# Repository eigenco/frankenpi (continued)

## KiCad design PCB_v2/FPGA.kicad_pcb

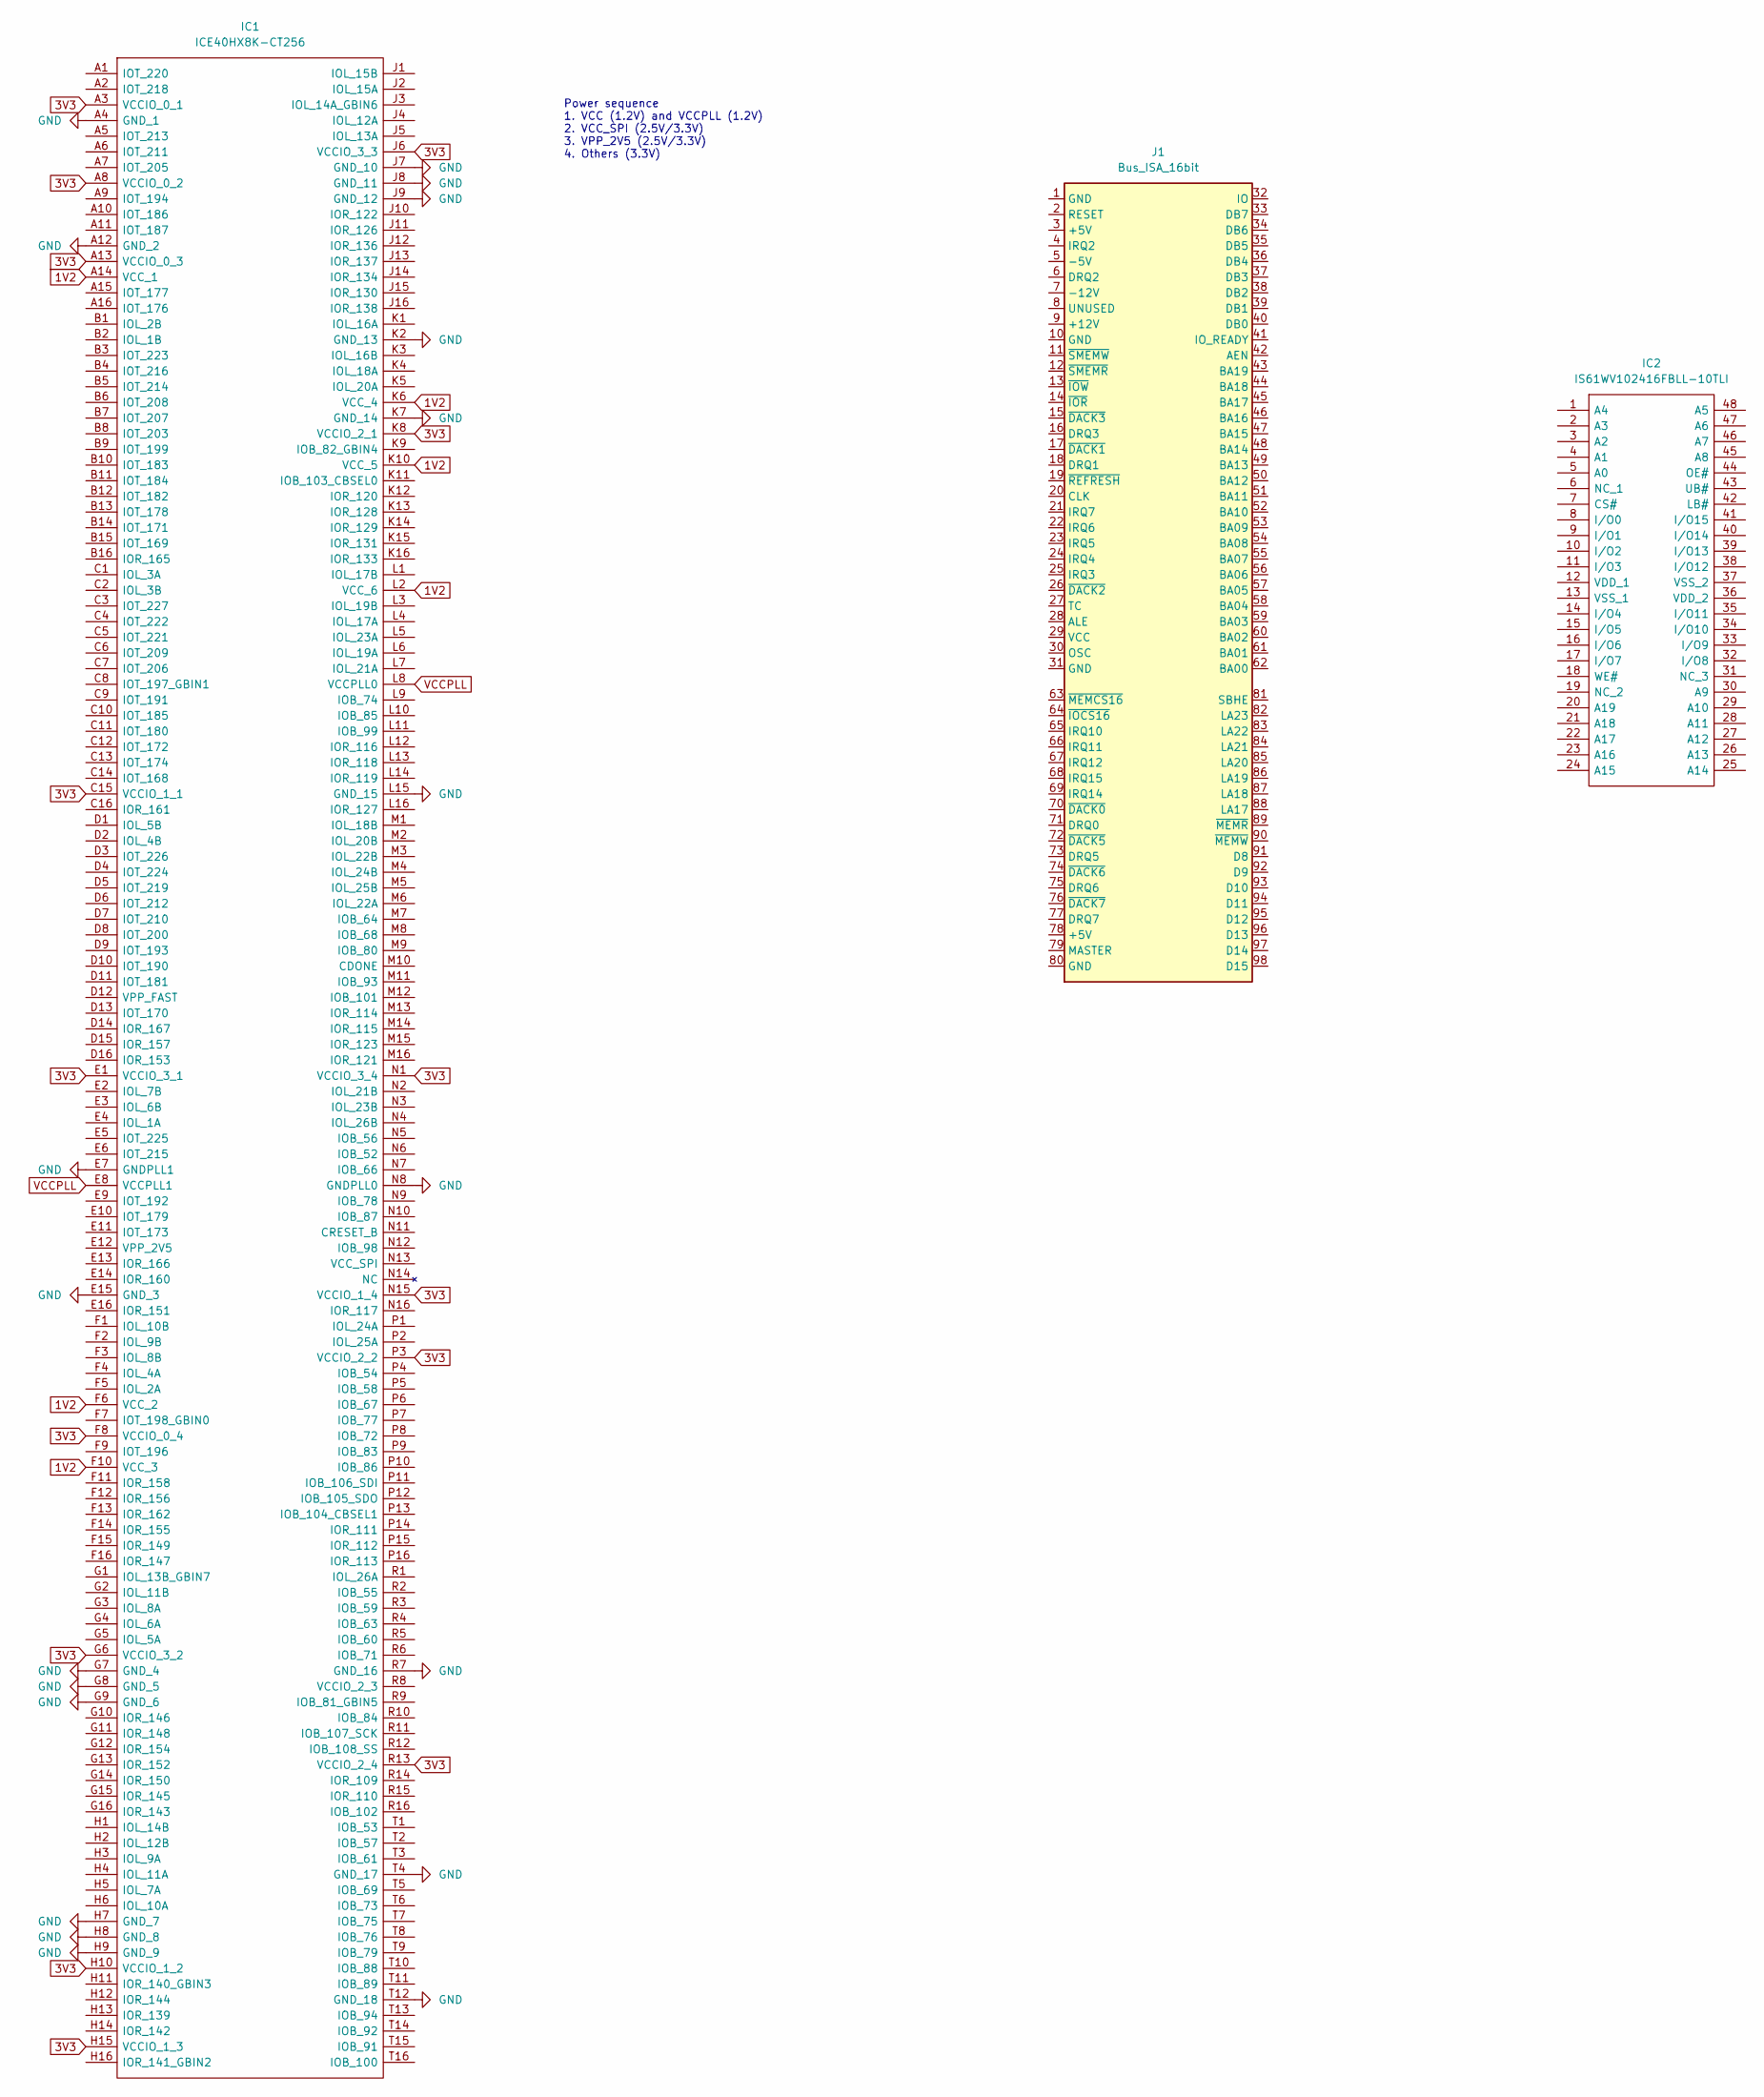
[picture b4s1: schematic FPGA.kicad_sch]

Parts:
IC1: ICE40HX8K-CT256; BGA256C80P16X16_1400X1400X170; Mouser Part Number 842-ICE40HX8K-CT256
IC2: IS61WV102416FBLL-10TLI; SOP50P2000X120-48N; Mouser Part Number 870-61WV12416FBL1TLI
J1: Bus_ISA_16bit; BUS_AT

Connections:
1V2: IC1.A14 (VCC_1), IC1.F6 (VCC_2), IC1.F10 (VCC_3), IC1.K6 (VCC_4), IC1.K10 (VCC_5), IC1.L2 (VCC_6)
3V3: IC1.A3 (VCCIO_0_1), IC1.A8 (VCCIO_0_2), IC1.A13 (VCCIO_0_3), IC1.C15 (VCCIO_1_1), IC1.E1 (VCCIO_3_1), IC1.F8 (VCCIO_0_4), IC1.G6 (VCCIO_3_2), IC1.H10 (VCCIO_1_2), IC1.H15 (VCCIO_1_3), IC1.J6 (VCCIO_3_3), IC1.K8 (VCCIO_2_1), IC1.N1 (VCCIO_3_4), IC1.N15 (VCCIO_1_4), IC1.P3 (VCCIO_2_2), IC1.R13 (VCCIO_2_4)
GND: IC1.A4 (GND_1), IC1.A12 (GND_2), IC1.E7 (GNDPLL1), IC1.E15 (GND_3), IC1.G7 (GND_4), IC1.G8 (GND_5), IC1.G9 (GND_6), IC1.H7 (GND_7), IC1.H8 (GND_8), IC1.H9 (GND_9), IC1.J7 (GND_10), IC1.J8 (GND_11), IC1.J9 (GND_12), IC1.K2 (GND_13), IC1.K7 (GND_14), IC1.L15 (GND_15), IC1.N8 (GNDPLL0), IC1.R7 (GND_16), IC1.T4 (GND_17), IC1.T12 (GND_18)
VCCPLL: IC1.E8 (VCCPLL1), IC1.L8 (VCCPLL0)

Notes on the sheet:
Power sequence 1. VCC (1.2V) and VCCPLL (1.2V) 2. VCC_SPI (2.5V/3.3V) 3. VPP_2V5 (2.5V/3.3V) 4. Others (3.3V)

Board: 2 copper layers, 3 parts (0 on the bottom side), 4 nets, no tracks yet.

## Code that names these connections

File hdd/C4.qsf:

# -------------------------------------------------------------------------- #
#
# Copyright (C) 1991-2013 Altera Corporation
# Your use of Altera Corporation's design tools, logic functions 
# and other software and tools, and its AMPP partner logic 
# functions, and any output files from any of the foregoing 
# (including device programming or simulation files), and any 
# associated documentation or information are expressly subject 
# to the terms and conditions of the Altera Program License 
# Subscription Agreement, Altera MegaCore Function License 
# Agreement, or other applicable license agreement, including, 
# without limitation, that your use is for the sole purpose of 
# programming logic devices manufactured by Altera and sold by 
# Altera or its authorized distributors.  Please refer to the 
# applicable agreement for further details.
#
# -------------------------------------------------------------------------- #
#
# Quartus II 64-Bit
# Version 13.0.1 Build 232 06/12/2013 Service Pack 1 SJ Web Edition
# Date created = 14:09:58  December 04, 2021
#
# -------------------------------------------------------------------------- #
#
# Notes:
#
# 1) The default values for assignments are stored in the file:
#		C4_assignment_defaults.qdf
#    If this file doesn't exist, see file:
#		assignment_defaults.qdf
#
# 2) Altera recommends that you do not modify this file. This
#    file is updated automatically by the Quartus II software
#    and any changes you make may be lost or overwritten.
#
# -------------------------------------------------------------------------- #


set_global_assignment -name FAMILY "Cyclone IV E"
set_global_assignment -name DEVICE EP4CE6E22C8
set_global_assignment -name TOP_LEVEL_ENTITY C4
set_global_assignment -name ORIGINAL_QUARTUS_VERSION "13.0 SP1"
set_global_assignment -name PROJECT_CREATION_TIME_DATE "14:09:58  DECEMBER 04, 2021"
set_global_assignment -name LAST_QUARTUS_VERSION "13.0 SP1"
set_global_assignment -name PROJECT_OUTPUT_DIRECTORY output_files
set_global_assignment -name MIN_CORE_JUNCTION_TEMP 0
set_global_assignment -name MAX_CORE_JUNCTION_TEMP 85
set_global_assignment -name ERROR_CHECK_FREQUENCY_DIVISOR 1
set_global_assignment -name NOMINAL_CORE_SUPPLY_VOLTAGE 1.2V

set_location_assignment PIN_25 -to clk
set_location_assignment PIN_138 -to leds[0]
set_location_assignment PIN_141 -to leds[1]
set_location_assignment PIN_142 -to leds[2]
set_location_assignment PIN_143 -to leds[3]
set_location_assignment PIN_144 -to leds[4]
set_location_assignment PIN_1 -to leds[5]
set_location_assignment PIN_2 -to leds[6]
set_location_assignment PIN_3 -to leds[7]

set_global_assignment -name PARTITION_NETLIST_TYPE SOURCE -section_id Top
set_global_assignment -name PARTITION_FITTER_PRESERVATION_LEVEL PLACEMENT_AND_ROUTING -section_id Top
set_global_assignment -name PARTITION_COLOR 16764057 -section_id Top
set_global_assignment -name STRATIX_DEVICE_IO_STANDARD "2.5 V"
set_location_assignment PIN_49 -to A[9]
set_location_assignment PIN_51 -to A[8]
set_location_assignment PIN_50 -to A[7]
set_location_assignment PIN_46 -to A[6]
set_location_assignment PIN_39 -to A[5]
set_location_assignment PIN_34 -to A[4]
set_location_assignment PIN_32 -to A[3]
set_location_assignment PIN_30 -to A[2]
set_location_assignment PIN_11 -to A[1]
set_location_assignment PIN_7 -to A[0]
set_location_assignment PIN_53 -to D[7]
set_location_assignment PIN_55 -to D[6]
set_location_assignment PIN_59 -to D[5]
set_location_assignment PIN_64 -to D[4]
set_location_assignment PIN_66 -to D[3]
set_location_assignment PIN_68 -to D[2]
set_location_assignment PIN_70 -to D[1]
set_location_assignment PIN_72 -to D[0]
set_location_assignment PIN_77 -to IOW
set_location_assignment PIN_80 -to IOR
set_location_assignment PIN_75 -to MEMW
set_location_assignment PIN_76 -to MEMR
set_location_assignment PIN_129 -to GPIO0
set_location_assignment PIN_126 -to GPIO1
set_location_assignment PIN_100 -to GPIO2
set_location_assignment PIN_85 -to GPIO3
set_location_assignment PIN_104 -to GPIO4
set_location_assignment PIN_128 -to GPIO5
set_location_assignment PIN_132 -to GPIO6
set_location_assignment PIN_127 -to GPIO7
set_location_assignment PIN_125 -to GPIO8
set_location_assignment PIN_120 -to GPIO9
set_location_assignment PIN_115 -to GPIO10
set_location_assignment PIN_67 -to IRQ2
set_location_assignment PIN_52 -to IRQ3
set_location_assignment PIN_54 -to IRQ4
set_location_assignment PIN_58 -to IRQ5
set_location_assignment PIN_60 -to IRQ6
set_location_assignment PIN_65 -to IRQ7
set_location_assignment PIN_33 -to DRQ1
set_location_assignment PIN_38 -to DACK1
set_location_assignment PIN_84 -to SPDIF
set_location_assignment PIN_124 -to GPIO11
set_location_assignment PIN_133 -to GPIO12
set_location_assignment PIN_136 -to GPIO13
set_location_assignment PIN_105 -to GPIO14
set_location_assignment PIN_110 -to GPIO15
set_location_assignment PIN_135 -to GPIO16
set_location_assignment PIN_106 -to GPIO17
set_location_assignment PIN_31 -to GPIO18
set_location_assignment PIN_28 -to GPIO19
set_location_assignment PIN_137 -to GPIO20
set_location_assignment PIN_10 -to GPIO21
set_location_assignment PIN_111 -to GPIO22
set_location_assignment PIN_119 -to GPIO24
set_location_assignment PIN_83 -to MIDI
set_global_assignment -name VERILOG_FILE spdif_core.v
set_global_assignment -name VERILOG_FILE C4.v
set_global_assignment -name QIP_FILE oRAM.qip
set_global_assignment -name QIP_FILE iRAM.qip
set_global_assignment -name QIP_FILE aFIFO.qip
set_global_assignment -name QIP_FILE PLL.qip
set_global_assignment -name POWER_PRESET_COOLING_SOLUTION "23 MM HEAT SINK WITH 200 LFPM AIRFLOW"
set_global_assignment -name POWER_BOARD_THERMAL_MODEL "NONE (CONSERVATIVE)"
set_global_assignment -name PHYSICAL_SYNTHESIS_REGISTER_RETIMING OFF
set_global_assignment -name PHYSICAL_SYNTHESIS_ASYNCHRONOUS_SIGNAL_PIPELINING OFF
set_location_assignment PIN_71 -to AEN
set_instance_assignment -name PARTITION_HIERARCHY root_partition -to | -section_id Top

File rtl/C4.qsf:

# -------------------------------------------------------------------------- #
#
# Copyright (C) 1991-2013 Altera Corporation
# Your use of Altera Corporation's design tools, logic functions 
# and other software and tools, and its AMPP partner logic 
# functions, and any output files from any of the foregoing 
# (including device programming or simulation files), and any 
# associated documentation or information are expressly subject 
# to the terms and conditions of the Altera Program License 
# Subscription Agreement, Altera MegaCore Function License 
# Agreement, or other applicable license agreement, including, 
# without limitation, that your use is for the sole purpose of 
# programming logic devices manufactured by Altera and sold by 
# Altera or its authorized distributors.  Please refer to the 
# applicable agreement for further details.
#
# -------------------------------------------------------------------------- #
#
# Quartus II 64-Bit
# Version 13.0.1 Build 232 06/12/2013 Service Pack 1 SJ Web Edition
# Date created = 14:09:58  December 04, 2021
#
# -------------------------------------------------------------------------- #
#
# Notes:
#
# 1) The default values for assignments are stored in the file:
#		C4_assignment_defaults.qdf
#    If this file doesn't exist, see file:
#		assignment_defaults.qdf
#
# 2) Altera recommends that you do not modify this file. This
#    file is updated automatically by the Quartus II software
#    and any changes you make may be lost or overwritten.
#
# -------------------------------------------------------------------------- #


set_global_assignment -name FAMILY "Cyclone IV E"
set_global_assignment -name DEVICE EP4CE6E22C8
set_global_assignment -name TOP_LEVEL_ENTITY C4
set_global_assignment -name ORIGINAL_QUARTUS_VERSION "13.0 SP1"
set_global_assignment -name PROJECT_CREATION_TIME_DATE "14:09:58  DECEMBER 04, 2021"
set_global_assignment -name LAST_QUARTUS_VERSION "13.0 SP1"
set_global_assignment -name PROJECT_OUTPUT_DIRECTORY output_files
set_global_assignment -name MIN_CORE_JUNCTION_TEMP 0
set_global_assignment -name MAX_CORE_JUNCTION_TEMP 85
set_global_assignment -name ERROR_CHECK_FREQUENCY_DIVISOR 1
set_global_assignment -name NOMINAL_CORE_SUPPLY_VOLTAGE 1.2V

set_location_assignment PIN_25 -to clk
set_location_assignment PIN_138 -to leds[0]
set_location_assignment PIN_141 -to leds[1]
set_location_assignment PIN_142 -to leds[2]
set_location_assignment PIN_143 -to leds[3]
set_location_assignment PIN_144 -to leds[4]
set_location_assignment PIN_1 -to leds[5]
set_location_assignment PIN_2 -to leds[6]
set_location_assignment PIN_3 -to leds[7]

set_global_assignment -name PARTITION_NETLIST_TYPE SOURCE -section_id Top
set_global_assignment -name PARTITION_FITTER_PRESERVATION_LEVEL PLACEMENT_AND_ROUTING -section_id Top
set_global_assignment -name PARTITION_COLOR 16764057 -section_id Top
set_global_assignment -name STRATIX_DEVICE_IO_STANDARD "2.5 V"
set_location_assignment PIN_49 -to A[9]
set_location_assignment PIN_51 -to A[8]
set_location_assignment PIN_50 -to A[7]
set_location_assignment PIN_46 -to A[6]
set_location_assignment PIN_39 -to A[5]
set_location_assignment PIN_34 -to A[4]
set_location_assignment PIN_32 -to A[3]
set_location_assignment PIN_30 -to A[2]
set_location_assignment PIN_11 -to A[1]
set_location_assignment PIN_7 -to A[0]
set_location_assignment PIN_53 -to D[7]
set_location_assignment PIN_55 -to D[6]
set_location_assignment PIN_59 -to D[5]
set_location_assignment PIN_64 -to D[4]
set_location_assignment PIN_66 -to D[3]
set_location_assignment PIN_68 -to D[2]
set_location_assignment PIN_70 -to D[1]
set_location_assignment PIN_72 -to D[0]
set_location_assignment PIN_77 -to IOW
set_location_assignment PIN_80 -to IOR
set_location_assignment PIN_75 -to MEMW
set_location_assignment PIN_76 -to MEMR
set_location_assignment PIN_129 -to GPIO0
set_location_assignment PIN_126 -to GPIO1
set_location_assignment PIN_100 -to GPIO2
set_location_assignment PIN_85 -to GPIO3
set_location_assignment PIN_104 -to GPIO4
set_location_assignment PIN_128 -to GPIO5
set_location_assignment PIN_132 -to GPIO6
set_location_assignment PIN_127 -to GPIO7
set_location_assignment PIN_125 -to GPIO8
set_location_assignment PIN_120 -to GPIO9
set_location_assignment PIN_115 -to GPIO10
set_location_assignment PIN_58 -to IRQ1
set_location_assignment PIN_67 -to IRQ2
set_location_assignment PIN_33 -to IRQ3
set_location_assignment PIN_38 -to IRQ4
set_location_assignment PIN_52 -to IRQ5
set_location_assignment PIN_54 -to IRQ7
set_location_assignment PIN_60 -to DRQ1
set_location_assignment PIN_65 -to DACK1

set_location_assignment PIN_10 -to OSC
set_location_assignment PIN_28 -to ISACLK
set_location_assignment PIN_42 -to A[10]
set_location_assignment PIN_31 -to A[11]


set_location_assignment PIN_83 -to RESET
set_location_assignment PIN_84 -to SPDIF
set_location_assignment PIN_124 -to GPIO11
set_location_assignment PIN_133 -to GPIO12
set_location_assignment PIN_136 -to GPIO13
set_location_assignment PIN_105 -to GPIO14
set_location_assignment PIN_110 -to GPIO15
set_location_assignment PIN_135 -to CLOCK
set_location_assignment PIN_106 -to FPGA_TX_REQ
set_location_assignment PIN_137 -to FPGA_RX_REQ
set_location_assignment PIN_111 -to STATE0
set_location_assignment PIN_114 -to STATE1
set_location_assignment PIN_119 -to STATE2
set_location_assignment PIN_69 -to AEN
set_location_assignment PIN_71 -to CHRDY

set_global_assignment -name VERILOG_FILE spdif_core.v
set_global_assignment -name VERILOG_FILE C4.v
set_global_assignment -name QIP_FILE oRAM.qip
set_global_assignment -name QIP_FILE iRAM.qip
set_global_assignment -name QIP_FILE aFIFO.qip
set_global_assignment -name QIP_FILE PLL.qip
set_global_assignment -name POWER_PRESET_COOLING_SOLUTION "23 MM HEAT SINK WITH 200 LFPM AIRFLOW"
set_global_assignment -name POWER_BOARD_THERMAL_MODEL "NONE (CONSERVATIVE)"
set_global_assignment -name PHYSICAL_SYNTHESIS_REGISTER_RETIMING OFF
set_global_assignment -name PHYSICAL_SYNTHESIS_ASYNCHRONOUS_SIGNAL_PIPELINING OFF
set_global_assignment -name TIMEQUEST_MULTICORNER_ANALYSIS OFF
set_global_assignment -name PHYSICAL_SYNTHESIS_REGISTER_DUPLICATION OFF
set_global_assignment -name QIP_FILE iFIFO.qip
set_global_assignment -name FITTER_EARLY_TIMING_ESTIMATE_MODE PESSIMISTIC
set_global_assignment -name CYCLONEII_OPTIMIZATION_TECHNIQUE SPEED
set_global_assignment -name SYNTH_TIMING_DRIVEN_SYNTHESIS ON
set_global_assignment -name OPTIMIZE_HOLD_TIMING "ALL PATHS"
set_global_assignment -name OPTIMIZE_MULTI_CORNER_TIMING ON
set_global_assignment -name FITTER_EFFORT "STANDARD FIT"
set_global_assignment -name PHYSICAL_SYNTHESIS_COMBO_LOGIC OFF
set_global_assignment -name PHYSICAL_SYNTHESIS_COMBO_LOGIC_FOR_AREA OFF
set_global_assignment -name PHYSICAL_SYNTHESIS_MAP_LOGIC_TO_MEMORY_FOR_AREA OFF
set_global_assignment -name SAFE_STATE_MACHINE ON
set_global_assignment -name REMOVE_REDUNDANT_LOGIC_CELLS ON
set_global_assignment -name SYNTH_PROTECT_SDC_CONSTRAINT ON
set_global_assignment -name PHYSICAL_SYNTHESIS_EFFORT EXTRA
set_global_assignment -name QIP_FILE mRAM.qip
set_global_assignment -name QIP_FILE optrom.qip
set_instance_assignment -name PARTITION_HIERARCHY root_partition -to | -section_id Top

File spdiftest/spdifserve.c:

// g++ -O3 -c opl.cpp
// gcc spdifserve.c opl.o -o spdifserve -lpthread -lm -lwiringPi
// GPIO0    D24 (L19)		D0
// GPIO1    D25 (K17)		D1
// GPIO2    D2  (M16)		D2
// GPIO3    D4  (D17)		D3
// GPIO4    D6  (K21)		D4
// GPIO5    NC  (conflicting)
// GPIO6    D26 (K19)		D6
// GPIO7    D23 (L17)		D7
// GPIO8    D21 (M18)
// GPIO9    D18 (L22)
// GPIO10   D16 (M22)
// GPIO11   D20 (P16)
// GPIO12   D27 (P18)
// GPIO13   D28 (R15)
// GPIO14   D7  (K22)
// GPIO15   D9  (M21)
// GPIO16   D31 (T20)		D5
// GPIO17   NC  (conflicting)
// GPIO18   NC  (conflicting)
// GPIO19   D30 (R16)		WRCLK (OUTPUT: FPGA audio FIFO write clock)
// GPIO20   D33 (T18)		WRREQ (OUTPUT: FPGA audio FIFO write request)
// GPIO21   D35 (T15)		AREQ  (INPUT: FPGA audio FIFO request)
// GPIO22   D12 (R21)
// GPIO23   D13 (T22)
// GPIO24   D15 (N19)
// GPIO25   D19 (P17)
// GPIO26   D32 (T19)
// GPIO27   D10 (N21)

#include <stdio.h>
#include <stdlib.h>
#include <stdint.h>
#include <unistd.h>
#include <pthread.h>
#include <wiringPi.h>

#define D0 0
#define D1 1
#define D2 2
#define D3 3
#define D4 4
#define D5 16
#define D6 6
#define D7 7
#define WRCLK 19
#define WRREQ 20
#define AREQ 21

void setdata(unsigned char data) {
  digitalWrite(D0, data & 1); data >>= 1;
  digitalWrite(D1, data & 1); data >>= 1;
  digitalWrite(D2, data & 1); data >>= 1;
  digitalWrite(D3, data & 1); data >>= 1;
  digitalWrite(D4, data & 1); data >>= 1;
  digitalWrite(D5, data & 1); data >>= 1;
  digitalWrite(D6, data & 1); data >>= 1;
  digitalWrite(D7, data & 1);
}

void adlib_init(uint32_t samplerate);
void adlib_write(uintptr_t idx, uint8_t val);
void adlib_getsample(int16_t* sndptr, intptr_t numsamples);

void adlib(void) {
  short buf[128];
  int i;
  for(;;) {
    while(digitalRead(AREQ)==0);
    digitalWrite(WRREQ, 1);
    digitalWrite(WRREQ, 1);
    digitalWrite(WRREQ, 1);
    digitalWrite(WRREQ, 1);
    for(i=0; i<64; i++) {
      setdata(buf[2*i]>>8);
      digitalWrite(WRCLK, 1);
      digitalWrite(WRCLK, 1);
      digitalWrite(WRCLK, 1);
      digitalWrite(WRCLK, 1);
      digitalWrite(WRCLK, 0);
      digitalWrite(WRCLK, 0);
      digitalWrite(WRCLK, 0);
      digitalWrite(WRCLK, 0);
      setdata(buf[2*i]&255);
      digitalWrite(WRCLK, 1);
      digitalWrite(WRCLK, 1);
      digitalWrite(WRCLK, 1);
      digitalWrite(WRCLK, 1);
      digitalWrite(WRCLK, 0);
      digitalWrite(WRCLK, 0);
      digitalWrite(WRCLK, 0);
      digitalWrite(WRCLK, 0);
    }
    digitalWrite(WRREQ, 0);
    digitalWrite(WRREQ, 0);
    digitalWrite(WRREQ, 0);
    digitalWrite(WRREQ, 0);
    adlib_getsample(buf, 64);
  }
}

int main() {
  pthread_t th;
  unsigned char buffer[57306];
  int song_register, song_data, song_offset = 0, song_wait;
  FILE *f;
  int i, j, k;

  wiringPiSetupGpio();
  for(i=0; i<28; i++)
    pinMode(i, OUTPUT);
  pinMode(AREQ, INPUT);

  adlib_init(48000);
  pthread_create(&th, NULL, (void*)adlib, NULL);

  f = fopen("lemmings.raw", "rb");
  fread(buffer, 1, 57306, f);
  fclose(f);

  for(;;) {
    song_register = buffer[song_offset];
    song_offset++;
    if(song_register==0) {
      song_wait  = (buffer[song_offset+1] << 8) | buffer[song_offset+0];
      song_offset += 2;
      usleep(1786*song_wait);
    } else {
      song_data = buffer[song_offset]; song_offset++;
      song_wait = buffer[song_offset]; song_offset++;
      adlib_write(song_register, song_data);
      usleep(1786*song_wait);
    }
    if(song_offset>57300) {
      for(i=0; i<256; i++)
        adlib_write(i, 0);
      exit(0);
    }
  }

  return 0;
}

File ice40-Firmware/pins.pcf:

set_io ISA_D[0] 139
set_io ISA_D[1] 141
set_io ISA_D[2] 142
set_io ISA_D[3] 143
set_io ISA_D[4] 144
set_io ISA_D[5] 1
set_io ISA_D[6] 2
set_io ISA_D[7] 3

set_io ISA_A[0] 104
set_io ISA_A[1] 105
set_io ISA_A[2] 106
set_io ISA_A[3] 107
set_io ISA_A[4] 112
set_io ISA_A[5] 113
set_io ISA_A[6] 114
set_io ISA_A[7] 115
set_io ISA_A[8] 116
set_io ISA_A[9] 117
set_io ISA_A[10] 118
set_io ISA_A[11] 119
set_io ISA_A[12] 120
set_io ISA_A[13] 121
set_io ISA_A[14] 122
set_io ISA_A[15] 128
set_io ISA_A[16] 129
set_io ISA_A[17] 134
set_io ISA_A[18] 135
set_io ISA_A[19] 136

set_io ISA_MEMW 97
set_io ISA_MEMR 98
set_io ISA_IOW 99
set_io ISA_IOR 101

set_io VGA_VS 7
set_io VGA_HS 8

set_io VGA_B[0] 9
set_io VGA_B[1] 10
set_io VGA_B[2] 11
set_io VGA_B[3] 12
set_io VGA_B[4] 19
set_io VGA_B[5] 20

set_io VGA_G[0] 21
set_io VGA_G[1] 22
set_io VGA_G[2] 23
set_io VGA_G[3] 24
set_io VGA_G[4] 25
set_io VGA_G[5] 26

set_io VGA_R[0] 28
set_io VGA_R[1] 29
set_io VGA_R[2] 31
set_io VGA_R[3] 32
set_io VGA_R[4] 33
set_io VGA_R[5] 34

set_io RPI_GPIO[0] 56
set_io RPI_GPIO[1] 58
set_io RPI_GPIO[2] 37
set_io RPI_GPIO[3] 38
set_io RPI_GPIO[4] 39
set_io RPI_GPIO[5] 60
set_io RPI_GPIO[6] 61
set_io RPI_GPIO[7] 52
set_io RPI_GPIO[8] 50
set_io RPI_GPIO[9] 67
set_io RPI_GPIO[10] 68
set_io RPI_GPIO[11] 70
set_io RPI_GPIO[12] 62
set_io RPI_GPIO[13] 49
set_io RPI_GPIO[14] 41
set_io RPI_GPIO[15] 42
set_io RPI_GPIO[16] 45
set_io RPI_GPIO[17] 43
set_io RPI_GPIO[18] 44
set_io RPI_GPIO[22] 47
set_io RPI_GPIO[23] 48
set_io RPI_GPIO[25] 71
set_io RPI_GPIO[27] 66

set_io ISA_RESET 63
set_io ISA_OSC 64
set_io ISA_IRQ4 74
set_io ISA_IRQ5 75
set_io ISA_IRQ7 76
set_io ISA_CLK 78
set_io ISA_DRQ1 79
set_io ISA_DACK1 80
set_io ISA_DRQ2 96
set_io ISA_DACK2 73
set_io ISA_DRQ3 81
set_io ISA_DACK3 102
set_io ISA_AEN 137
set_io ISA_READY 138

set_io CLK 93

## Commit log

2022-12-22 started new pcb design
